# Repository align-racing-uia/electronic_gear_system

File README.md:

<h1 align="center"> Electronic Gear System </h1> <br>
<p align="center">
    
</p>

<!-- START doctoc generate TOC please keep comment here to allow auto update -->
<!-- DON'T EDIT THIS SECTION, INSTEAD RE-RUN doctoc TO UPDATE -->
## Table of contents

- [Introduction](#introduction)
- [Align Racing UiA](#alignracinguia)
- [Rules for file structure](#rulesforfilestructure)
- [License](#license)

<!-- END doctoc generated TOC please keep comment here to allow auto update -->

## Introduction

This is the repository for Align Racing's formula student race car's different systems.

## Align Racing UiA

<a href="http://www.alignracing.no/">Align Racing UiA (AR)</a> is a multidisciplinary student organisation at <a href="https://www.uia.no/">The University of Agder (UiA)</a>, that take part in the world’s largest yearly engineering competition; <a href="https://www.imeche.org/events/formula-student">Formula Student (FS)</a>. The organisation continuously consists of around 60 students, from a wide variety of disciplines. The competition includes developing, building, budgeting and marketing a small scale formula type racing car. AR takes this a bit further by having more focus on developing a strong organisation, open for all disciplines, that gives the members a taste of future work-life.

## Rules

## Contribution

## License
All content included in this Git repository is under the license:

Creative Commons Attribution-NonCommercial-ShareAlike 4.0 International

You are free to:
* <b> Share </b> — copy and redistribute the material in any medium or format
* <b> Adapt </b> — remix, transform, and build upon the material

Under the following terms:
* <b> Attribution </b> — You must give appropriate credit, provide a link to the license, and indicate if changes were made. You may do so in any reasonable manner, but not in any way that suggests the licensor endorses you or your use.
* <b> NonCommercial </b> — You may not use the material for commercial purposes.
* <b> ShareAlike </b> — If you remix, transform, or build upon the material, you must distribute your contributions under the same license as the original.
* <b> No additional restrictions </b> — You may not apply legal terms or technological measures that legally restrict others from doing anything the license permits.

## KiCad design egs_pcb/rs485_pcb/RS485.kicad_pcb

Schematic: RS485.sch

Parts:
C1: 0.1uF; C_0402_1005Metric
D1: MM3Z3V6T1G; D_SOD-323
D2: MBR0520LT; D_SOD-123
J1: Conn_01x06_Female; PinSocket_1x06_P1.00mm_Vertical
J2: Conn_01x02_Female; PinSocket_1x02_P1.00mm_Vertical
Q1: PMOS_SQ2309ES-T1_GE3; PMOS_SQ2309ES
R1: R120Ω; C_0603_1608Metric
R2: R10kΩ; C_0603_1608Metric
U1: MAX3362EKA+T

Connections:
3.3_filtered: C1.2, D1.1, D2.1 (K), Q1.2, U1.8
*RX_Enable: J1.3, U1.2
+3V3: J1.1, Q1.3
/A: J2.1, R1.2, U1.6
/B: J2.2, R1.1, U1.7
GND: C1.1, D1.2, J1.6, R2.2, U1.5
unnamed: D2.2 (A), Q1.1, R2.1
RX: J1.2, U1.1
TX: J1.5, U1.4
TX_Enable: J1.4, U1.3

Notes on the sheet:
Reverse polarity protection

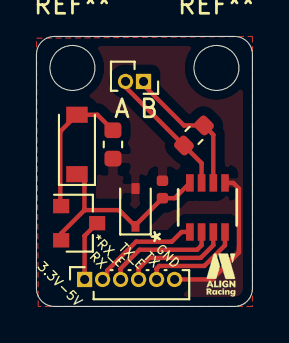
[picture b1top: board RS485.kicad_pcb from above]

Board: 2 copper layers, 12.0 x 15.0 mm, 9 parts (0 on the bottom side), 10 nets.

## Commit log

2021-08-01 Merged: EGS, EGS_servo and EGS_main_logic. And directory refactor.
2021-08-01 Added: Title in README.md

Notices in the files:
parts and their libraries:
Copyright 2016 Accelerated Designs. All rights reserved.
